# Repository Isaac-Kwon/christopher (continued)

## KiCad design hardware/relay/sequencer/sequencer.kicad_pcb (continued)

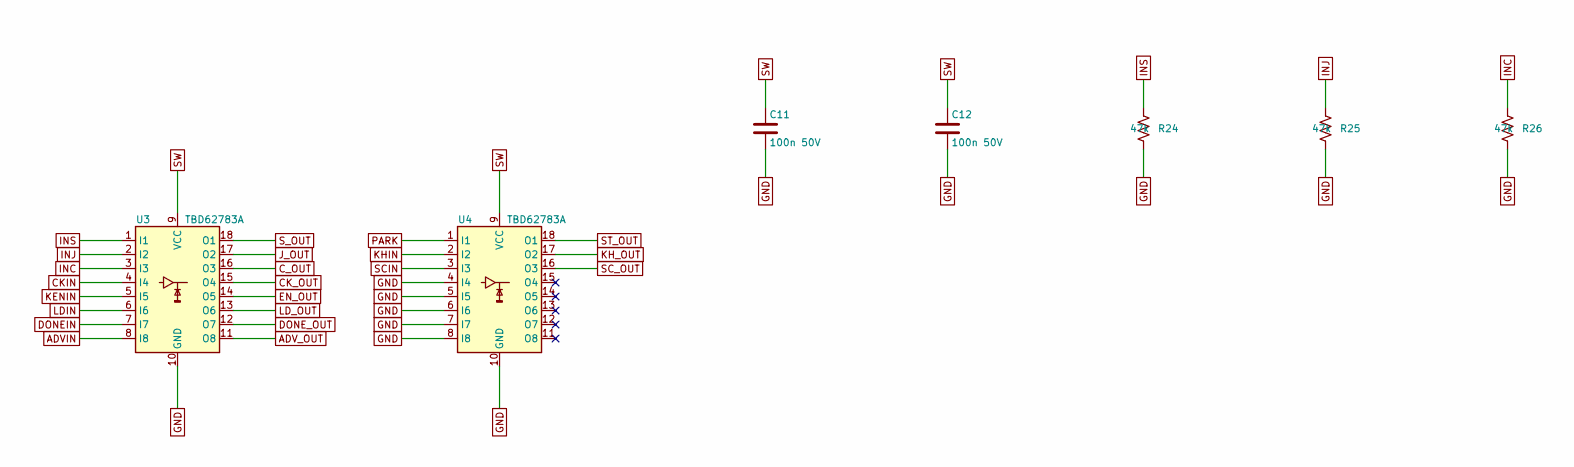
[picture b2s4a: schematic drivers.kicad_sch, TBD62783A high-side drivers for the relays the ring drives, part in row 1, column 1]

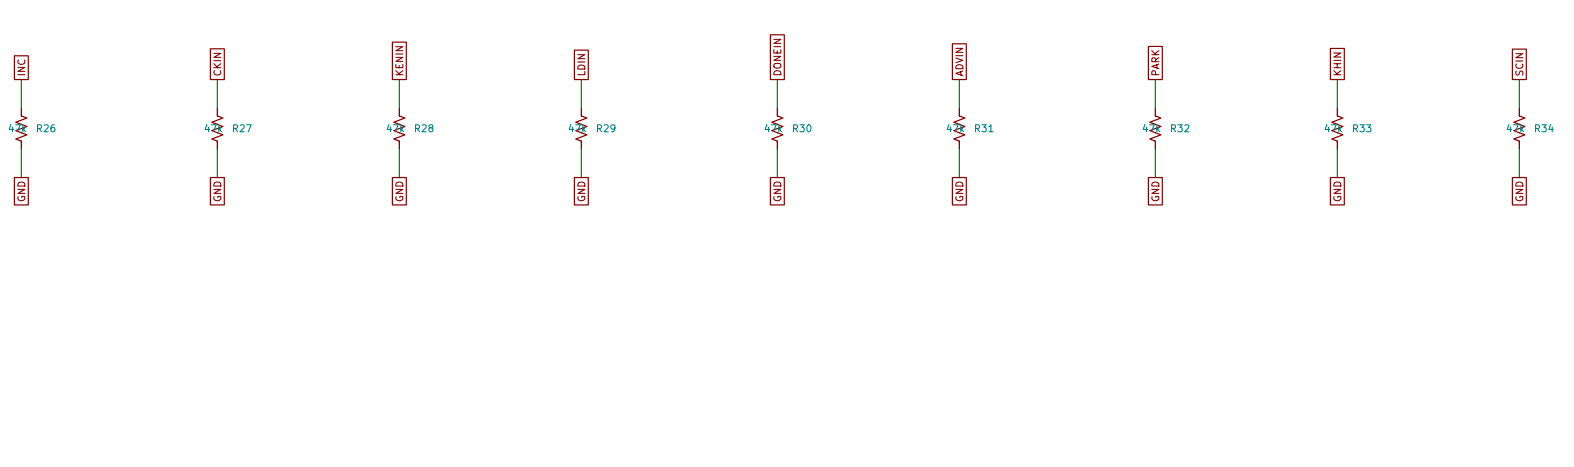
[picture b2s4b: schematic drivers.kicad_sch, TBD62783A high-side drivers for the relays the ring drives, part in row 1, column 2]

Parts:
C11, C12: 100n 50V; C_0805_2012Metric
R24, R25, R26, R27, R28, R29, R30, R31, R32, R33, R34: 47k; R_0603_1608Metric
U3, U4: TBD62783A; SOIC-18W_7.5x11.6mm_P1.27mm

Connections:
ADVIN: R31.1, U3.8 (I8); also elsewhere on the board
ADV_OUT: U3.11 (O8); also elsewhere on the board
CKIN: R27.1, U3.4 (I4); also elsewhere on the board
CK_OUT: U3.15 (O4); also elsewhere on the board
C_OUT: U3.16 (O3); also elsewhere on the board
DONEIN: R30.1, U3.7 (I7); also elsewhere on the board
DONE_OUT: U3.12 (O7); also elsewhere on the board
EN_OUT: U3.14 (O5); also elsewhere on the board
GND: C11.2, C12.2, R24.2, R25.2, R26.2, R27.2, R28.2, R29.2, R30.2, R31.2, R32.2, R33.2, R34.2, U3.10 (GND), U4.4 (I4), U4.5 (I5), U4.6 (I6), U4.7 (I7), U4.8 (I8), U4.10 (GND); also elsewhere on the board
INC: R26.1, U3.3 (I3); also elsewhere on the board
INJ: R25.1, U3.2 (I2); also elsewhere on the board
INS: R24.1, U3.1 (I1); also elsewhere on the board
J_OUT: U3.17 (O2); also elsewhere on the board
KENIN: R28.1, U3.5 (I5); also elsewhere on the board
KHIN: R33.1, U4.2 (I2); also elsewhere on the board
KH_OUT: U4.17 (O2); also elsewhere on the board
LDIN: R29.1, U3.6 (I6); also elsewhere on the board
LD_OUT: U3.13 (O6); also elsewhere on the board
PARK: R32.1, U4.1 (I1); also elsewhere on the board
SCIN: R34.1, U4.3 (I3); also elsewhere on the board
SC_OUT: U4.16 (O3); also elsewhere on the board
ST_OUT: U4.18 (O1); also elsewhere on the board
SW: C11.1, C12.1, U3.9 (VCC), U4.9 (VCC); also elsewhere on the board
S_OUT: U3.18 (O1); also elsewhere on the board

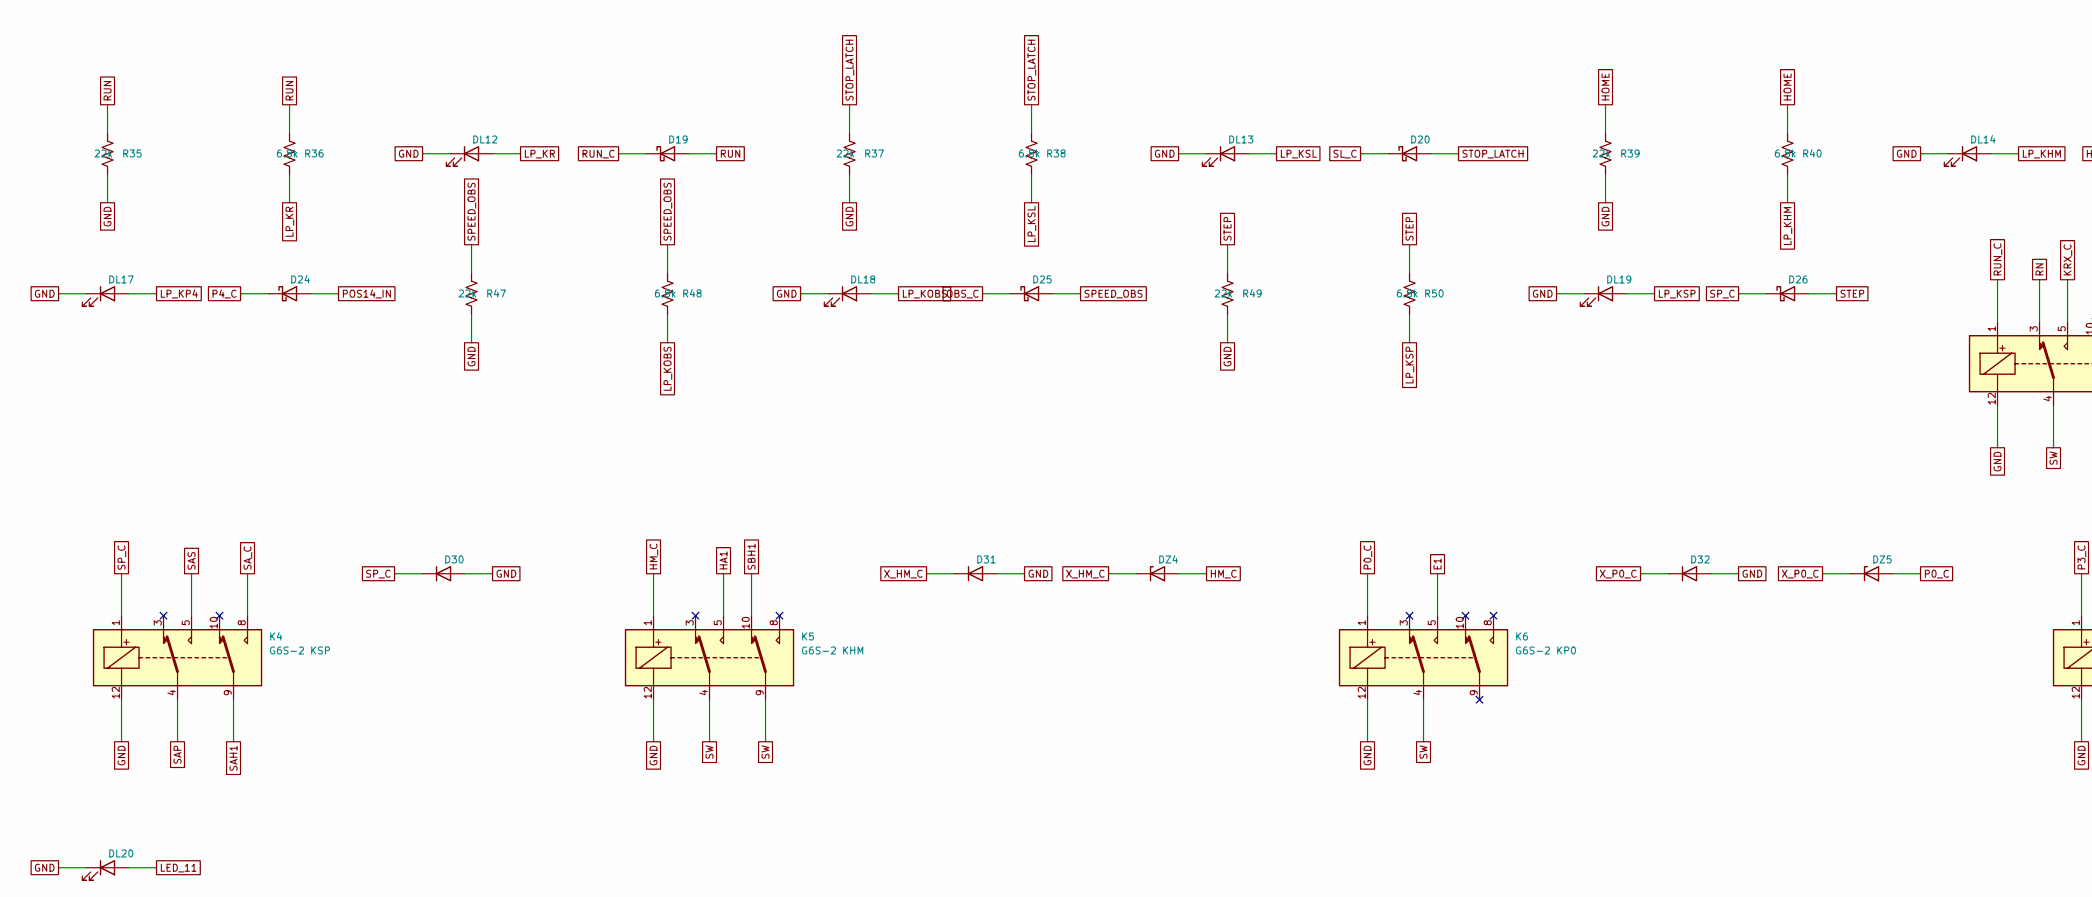
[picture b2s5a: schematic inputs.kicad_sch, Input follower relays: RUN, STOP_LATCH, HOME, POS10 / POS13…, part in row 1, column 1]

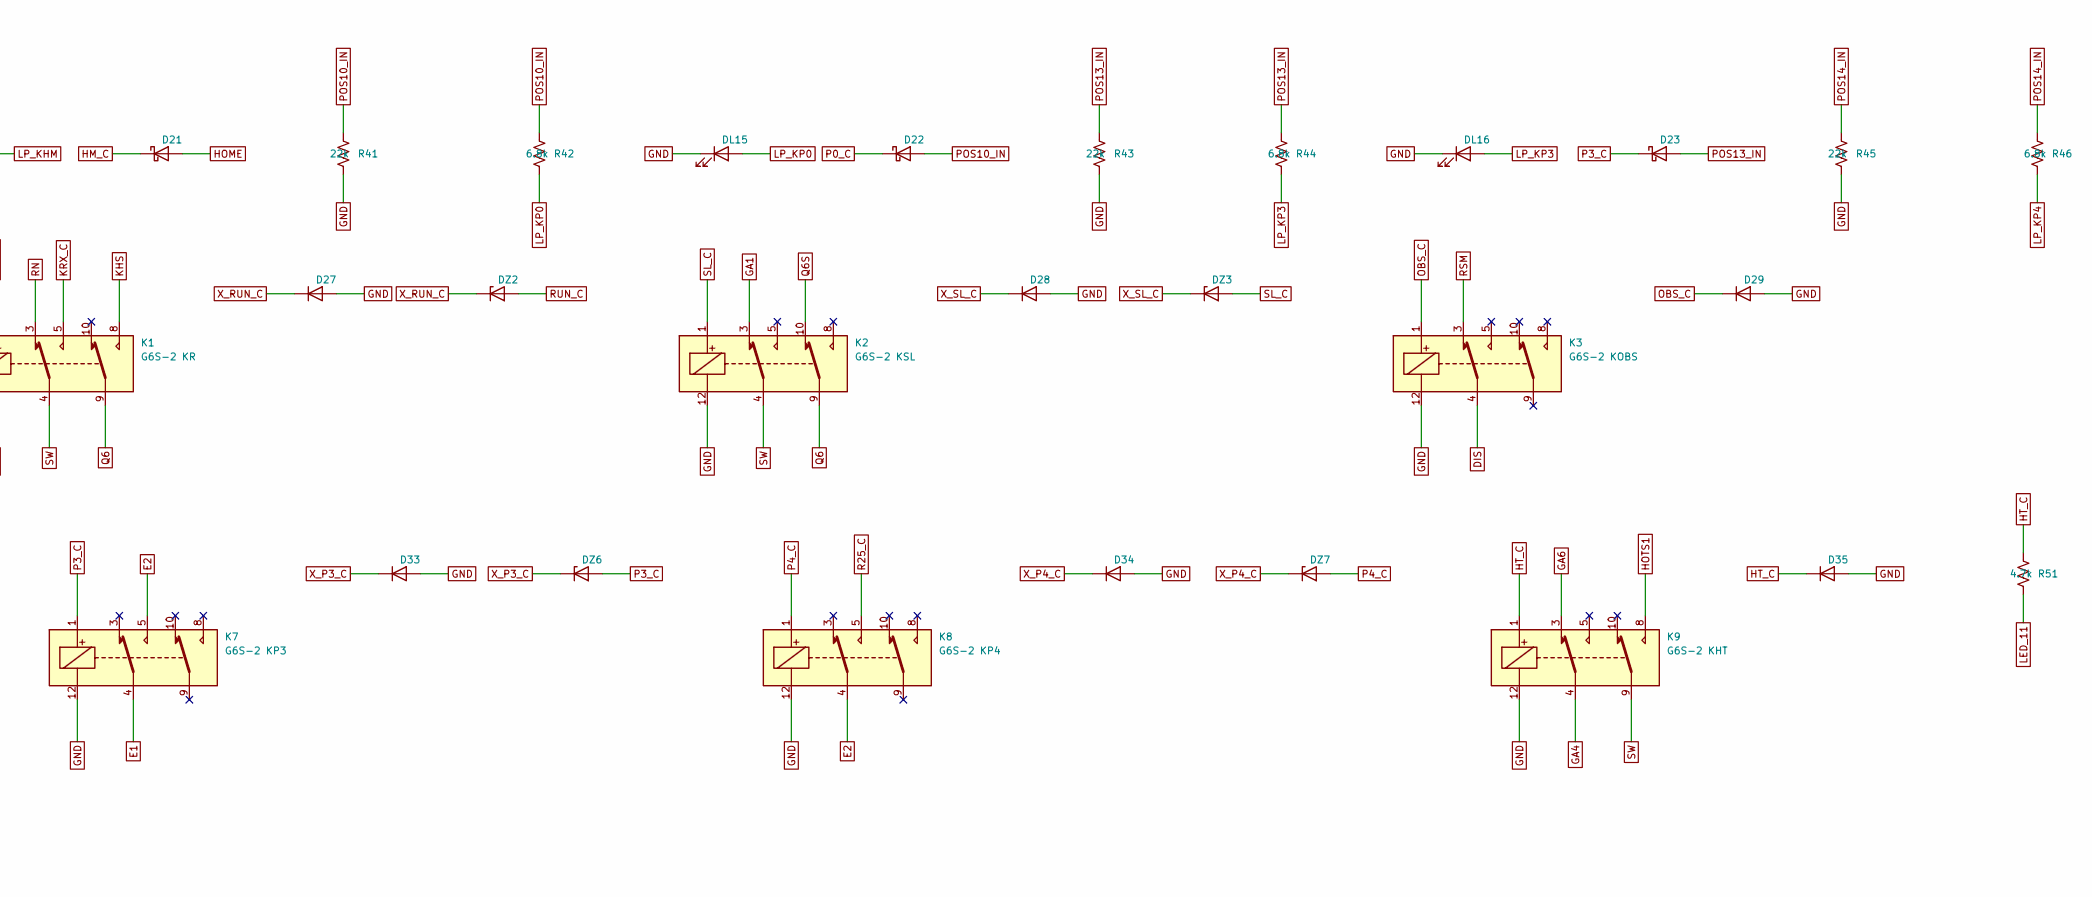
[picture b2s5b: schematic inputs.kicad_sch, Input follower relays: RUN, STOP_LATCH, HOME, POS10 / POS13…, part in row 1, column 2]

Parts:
D19, D20, D21, D22, D23, D24, D25, D26: BAT54 / SS14 Schottky; D_SOD-123
D27, D28, D29, D30, D31, D32, D33, D34, D35: 1N4148W; D_SOD-123
DL12, DL13, DL14, DL15, DL16, DL17, DL18, DL19, DL20: LED; LED_0603_1608Metric
DZ2, DZ3, DZ4, DZ5, DZ6, DZ7: BZT52C30; D_SOD-123
K1: G6S-2 KR; Relay_DPDT_Omron_G6S-2
K2: G6S-2 KSL; Relay_DPDT_Omron_G6S-2
K3: G6S-2 KOBS; Relay_DPDT_Omron_G6S-2
K4: G6S-2 KSP; Relay_DPDT_Omron_G6S-2
K5: G6S-2 KHM; Relay_DPDT_Omron_G6S-2
K6: G6S-2 KP0; Relay_DPDT_Omron_G6S-2
K7: G6S-2 KP3; Relay_DPDT_Omron_G6S-2
K8: G6S-2 KP4; Relay_DPDT_Omron_G6S-2
K9: G6S-2 KHT; Relay_DPDT_Omron_G6S-2
R35, R37, R39, R41, R43, R45, R47, R49: 22k; R_0603_1608Metric
R36, R38, R40, R42, R44, R46, R48, R50: 6.8k; R_0603_1608Metric
R51: 4.7k; R_0603_1608Metric

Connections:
DIS: K3.4; also elsewhere on the board
E1: K6.5, K7.4
E2: K7.5, K8.4
GA1: K2.3; also elsewhere on the board
GA4: K9.4; also elsewhere on the board
GA6: K9.3; also elsewhere on the board
GND: D27.2 (A), D28.2 (A), D29.2 (A), D30.2 (A), D31.2 (A), D32.2 (A), D33.2 (A), D34.2 (A), D35.2 (A), DL12.1 (K), DL13.1 (K), DL14.1 (K), DL15.1 (K), DL16.1 (K), DL17.1 (K), DL18.1 (K), DL19.1 (K), DL20.1 (K), K1.12, K2.12, K3.12, K4.12, K5.12, K6.12, K7.12, K8.12, K9.12, R35.2, R37.2, R39.2, R41.2, R43.2, R45.2, R47.2, R49.2; also elsewhere on the board
HA1: K5.5; also elsewhere on the board
HM_C: D21.1 (K), DZ4.2 (A), K5.1
HOME: D21.2 (A), R39.1, R40.1; also elsewhere on the board
HOTS1: K9.8; also elsewhere on the board
HT_C: D35.1 (K), K9.1, R51.1; also elsewhere on the board
KHS: K1.8; also elsewhere on the board
KRX_C: K1.5; also elsewhere on the board
LED_11: DL20.2 (A), R51.2
LP_KHM: DL14.2 (A), R40.2
LP_KOBS: DL18.2 (A), R48.2
LP_KP0: DL15.2 (A), R42.2
LP_KP3: DL16.2 (A), R44.2
LP_KP4: DL17.2 (A), R46.2
LP_KR: DL12.2 (A), R36.2
LP_KSL: DL13.2 (A), R38.2
LP_KSP: DL19.2 (A), R50.2
OBS_C: D25.1 (K), D29.1 (K), K3.1
P0_C: D22.1 (K), DZ5.2 (A), K6.1
P3_C: D23.1 (K), DZ6.2 (A), K7.1
P4_C: D24.1 (K), DZ7.2 (A), K8.1
POS10_IN: D22.2 (A), R41.1, R42.1; also elsewhere on the board
POS13_IN: D23.2 (A), R43.1, R44.1; also elsewhere on the board
POS14_IN: D24.2 (A), R45.1, R46.1; also elsewhere on the board
Q6: K1.9, K2.9; also elsewhere on the board
Q6S: K2.10; also elsewhere on the board
R25_C: K8.5; also elsewhere on the board
RN: K1.3; also elsewhere on the board
RSM: K3.3; also elsewhere on the board
RUN: D19.2 (A), R35.1, R36.1; also elsewhere on the board
RUN_C: D19.1 (K), DZ2.2 (A), K1.1
SAH1: K4.9; also elsewhere on the board
SAP: K4.4; also elsewhere on the board
SAS: K4.5; also elsewhere on the board
SA_C: K4.8; also elsewhere on the board
SBH1: K5.10; also elsewhere on the board
SL_C: D20.1 (K), DZ3.2 (A), K2.1
SPEED_OBS: D25.2 (A), R47.1, R48.1; also elsewhere on the board
SP_C: D26.1 (K), D30.1 (K), K4.1
STEP: D26.2 (A), R49.1, R50.1; also elsewhere on the board
STOP_LATCH: D20.2 (A), R37.1, R38.1; also elsewhere on the board
SW: K1.4, K2.4, K5.4, K5.9, K6.4, K9.9; also elsewhere on the board
X_HM_C: D31.1 (K), DZ4.1 (K)
X_P0_C: D32.1 (K), DZ5.1 (K)
X_P3_C: D33.1 (K), DZ6.1 (K)
X_P4_C: D34.1 (K), DZ7.1 (K)
X_RUN_C: D27.1 (K), DZ2.1 (K)
X_SL_C: D28.1 (K), DZ3.1 (K)

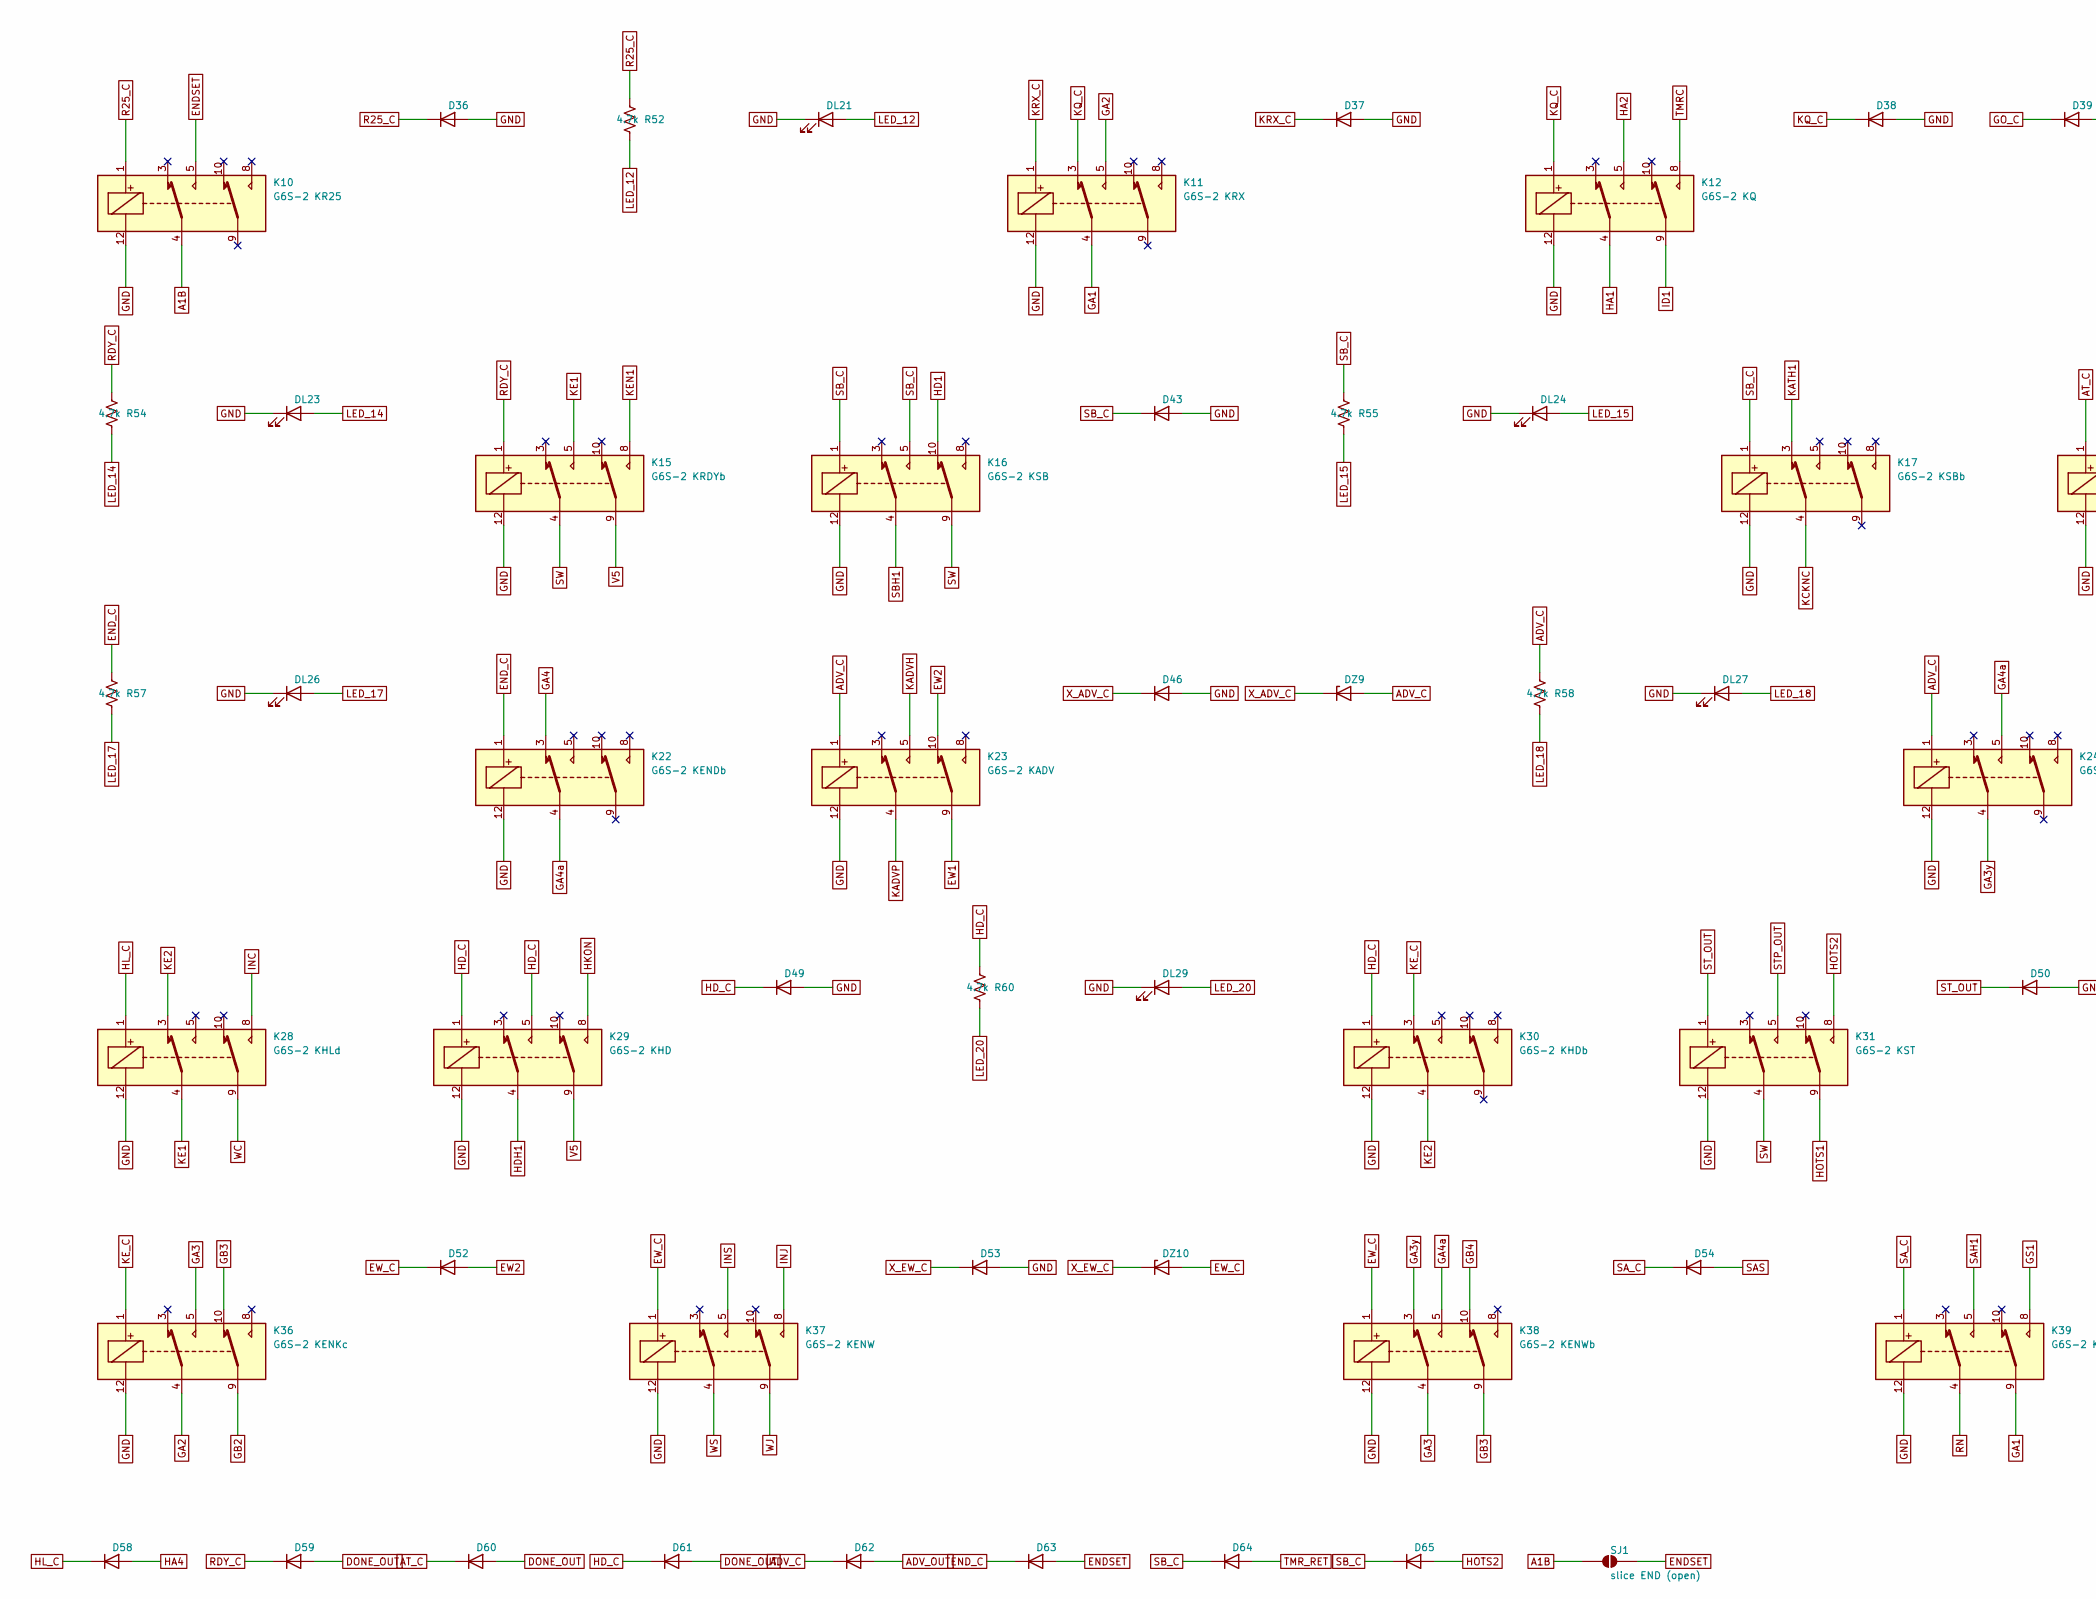
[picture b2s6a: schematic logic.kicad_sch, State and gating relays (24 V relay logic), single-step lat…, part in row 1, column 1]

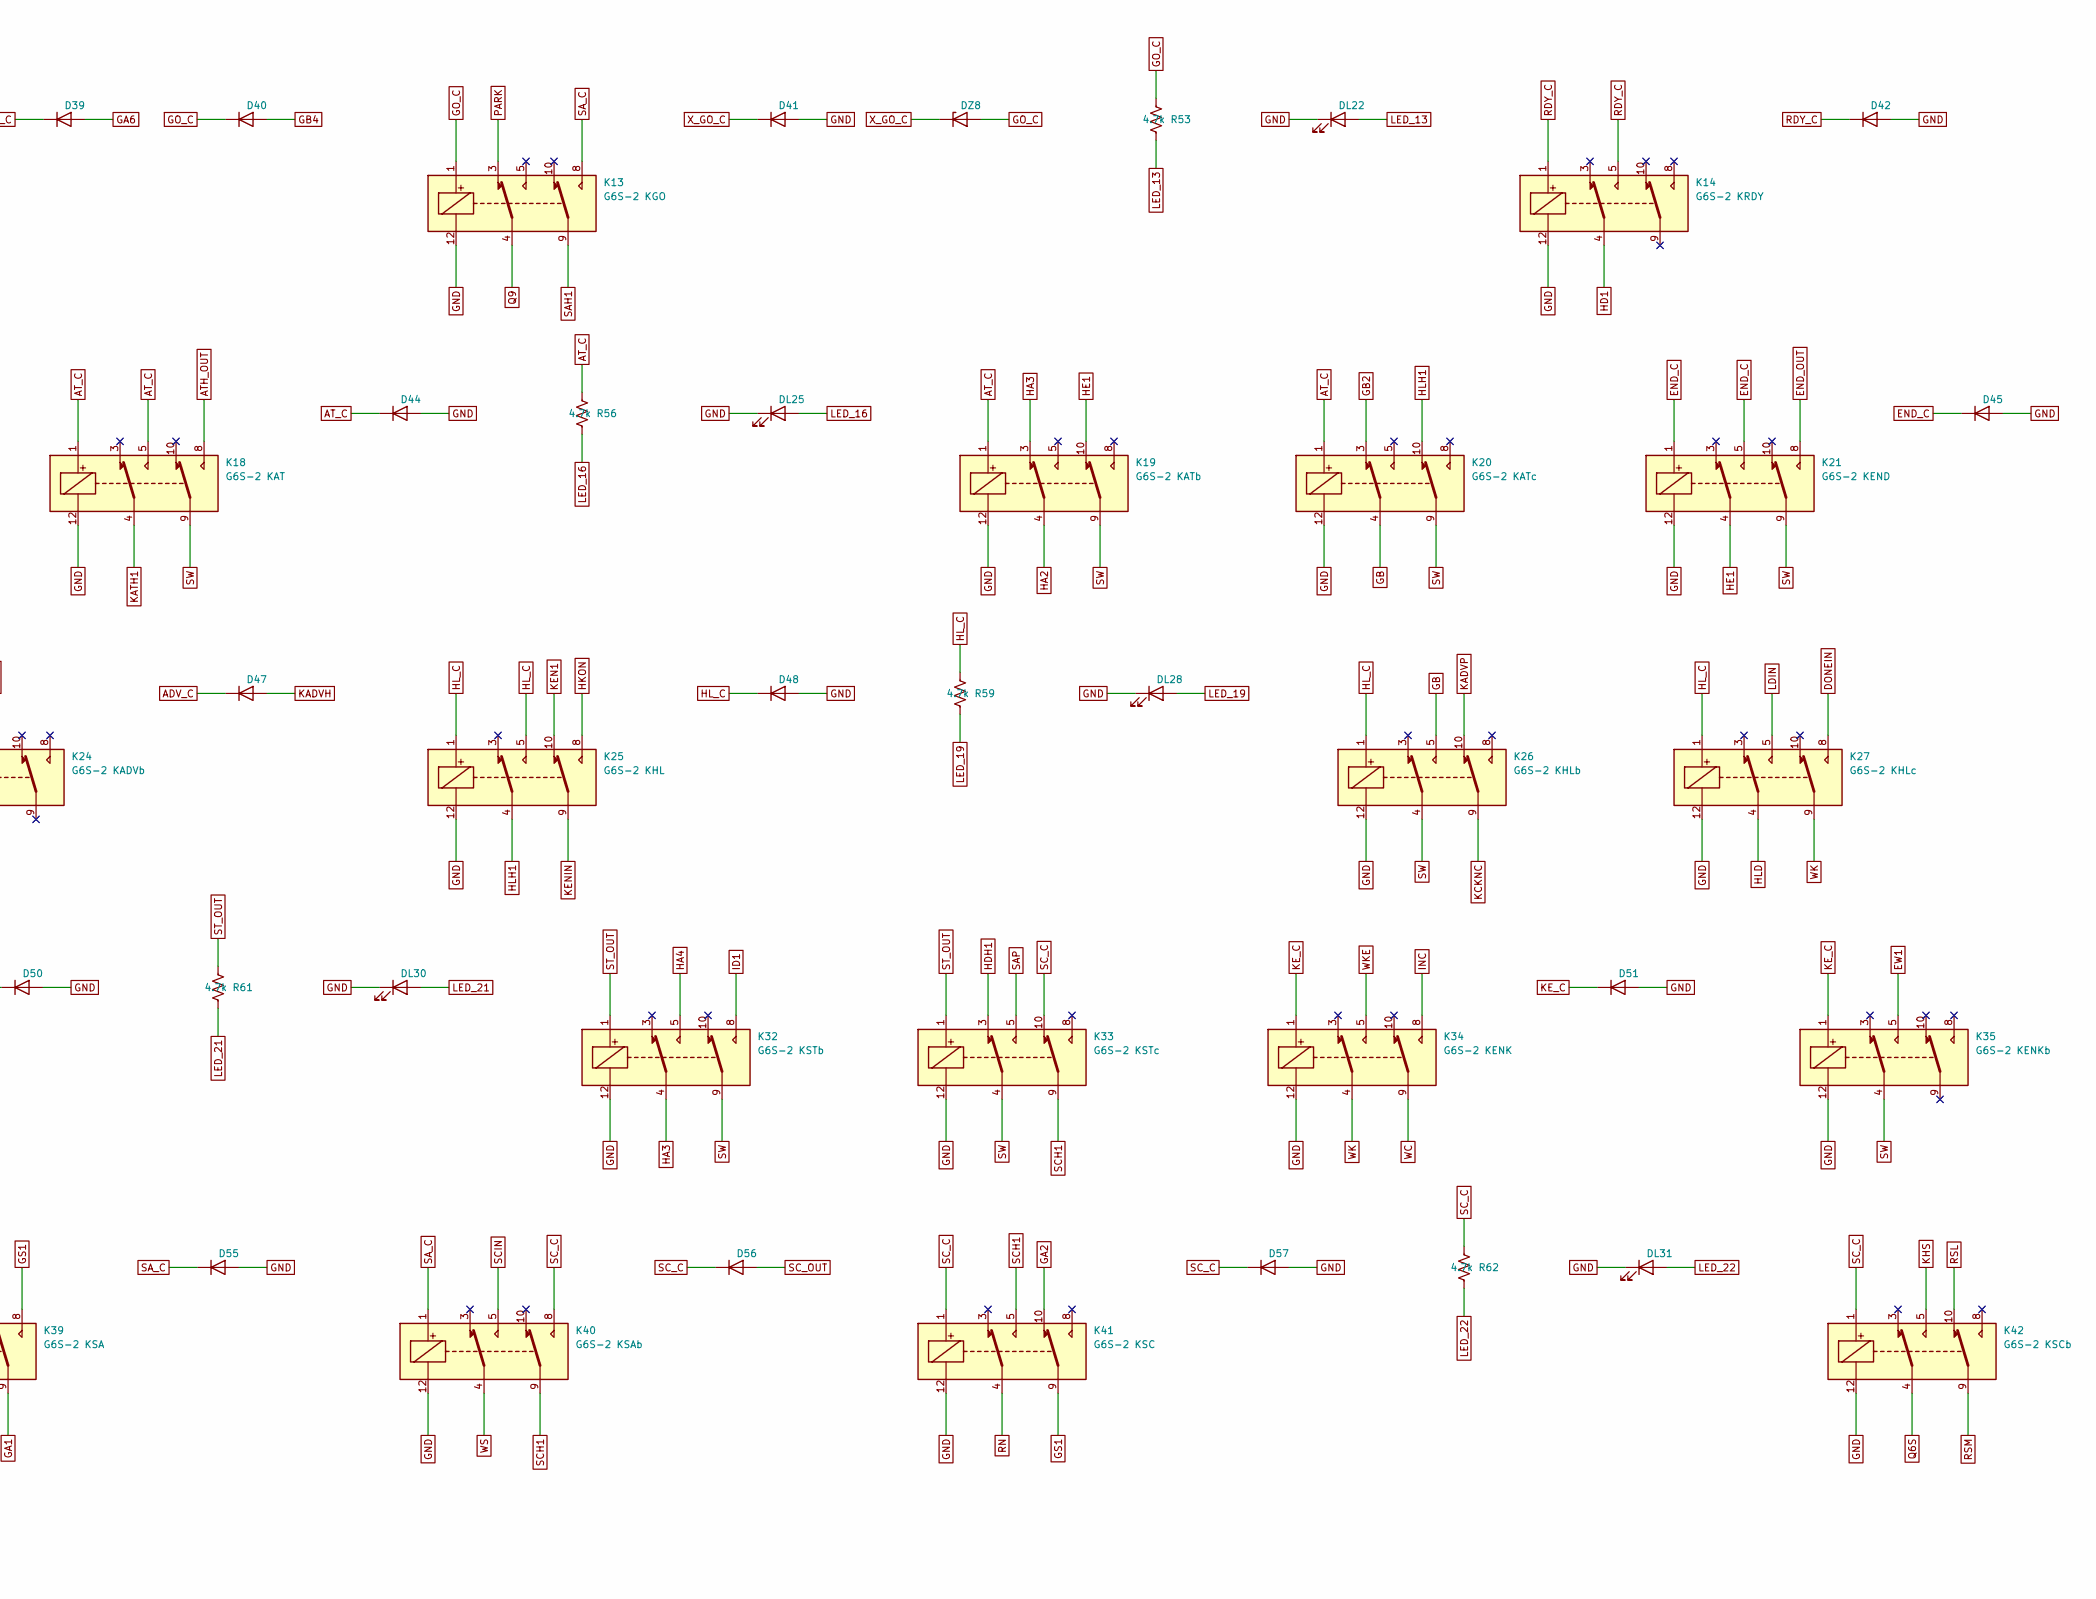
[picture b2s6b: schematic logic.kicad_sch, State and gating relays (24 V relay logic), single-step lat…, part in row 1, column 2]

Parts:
D36, D37, D38, D39, D40, D41, D42, D43, D44, D45, D46, D47, D48, D49, D50, D51, D52, D53, D54, D55, D56, D57, D58, D59, D60, D61, D62, D63, D64, D65: 1N4148W; D_SOD-123
DL21, DL22, DL23, DL24, DL25, DL26, DL27, DL28, DL29, DL30, DL31: LED; LED_0603_1608Metric
DZ8, DZ9, DZ10: BZT52C30; D_SOD-123
K10: G6S-2 KR25; Relay_DPDT_Omron_G6S-2
K11: G6S-2 KRX; Relay_DPDT_Omron_G6S-2
K12: G6S-2 KQ; Relay_DPDT_Omron_G6S-2
K13: G6S-2 KGO; Relay_DPDT_Omron_G6S-2
K14: G6S-2 KRDY; Relay_DPDT_Omron_G6S-2
K15: G6S-2 KRDYb; Relay_DPDT_Omron_G6S-2
K16: G6S-2 KSB; Relay_DPDT_Omron_G6S-2
K17: G6S-2 KSBb; Relay_DPDT_Omron_G6S-2
K18: G6S-2 KAT; Relay_DPDT_Omron_G6S-2
K19: G6S-2 KATb; Relay_DPDT_Omron_G6S-2
K20: G6S-2 KATc; Relay_DPDT_Omron_G6S-2
K21: G6S-2 KEND; Relay_DPDT_Omron_G6S-2
K22: G6S-2 KENDb; Relay_DPDT_Omron_G6S-2
K23: G6S-2 KADV; Relay_DPDT_Omron_G6S-2
K24: G6S-2 KADVb; Relay_DPDT_Omron_G6S-2
K25: G6S-2 KHL; Relay_DPDT_Omron_G6S-2
K26: G6S-2 KHLb; Relay_DPDT_Omron_G6S-2
K27: G6S-2 KHLc; Relay_DPDT_Omron_G6S-2
K28: G6S-2 KHLd; Relay_DPDT_Omron_G6S-2
K29: G6S-2 KHD; Relay_DPDT_Omron_G6S-2
K30: G6S-2 KHDb; Relay_DPDT_Omron_G6S-2
K31: G6S-2 KST; Relay_DPDT_Omron_G6S-2
K32: G6S-2 KSTb; Relay_DPDT_Omron_G6S-2
K33: G6S-2 KSTc; Relay_DPDT_Omron_G6S-2
K34: G6S-2 KENK; Relay_DPDT_Omron_G6S-2
K35: G6S-2 KENKb; Relay_DPDT_Omron_G6S-2
K36: G6S-2 KENKc; Relay_DPDT_Omron_G6S-2
K37: G6S-2 KENW; Relay_DPDT_Omron_G6S-2
K38: G6S-2 KENWb; Relay_DPDT_Omron_G6S-2
K39: G6S-2 KSA; Relay_DPDT_Omron_G6S-2
K40: G6S-2 KSAb; Relay_DPDT_Omron_G6S-2
K41: G6S-2 KSC; Relay_DPDT_Omron_G6S-2
K42: G6S-2 KSCb; Relay_DPDT_Omron_G6S-2
R52, R53, R54, R55, R56, R57, R58, R59, R60, R61, R62: 4.7k; R_0603_1608Metric
SJ1: slice END (open); SolderJumper-2_P1.3mm_Open_RoundedPad1.0x1.5mm

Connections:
A1B: K10.4, SJ1.1 (A); also elsewhere on the board
ADV_C: D47.1 (K), D62.1 (K), DZ9.2 (A), K23.1, K24.1, R58.1
ADV_OUT: D62.2 (A); also elsewhere on the board
ATH_OUT: K18.8; also elsewhere on the board
AT_C: D44.1 (K), D60.1 (K), K18.1, K18.5, K19.1, K20.1, R56.1
DONEIN: K27.8; also elsewhere on the board
DONE_OUT: D59.2 (A), D60.2 (A), D61.2 (A); also elsewhere on the board
ENDSET: D63.2 (A), K10.5, SJ1.2 (B)
END_C: D45.1 (K), D63.1 (K), K21.1, K21.5, K22.1, R57.1
END_OUT: K21.8; also elsewhere on the board
EW1: K23.9, K35.5
EW2: D52.2 (A), K23.10
EW_C: D52.1 (K), DZ10.2 (A), K37.1, K38.1
GA1: K11.4, K39.9; also elsewhere on the board
GA2: K11.5, K36.4, K41.10
GA3: K36.5, K38.4
GA3y: K24.4, K38.3
GA4: K22.3; also elsewhere on the board
GA4a: K22.4, K24.5, K38.5
GA6: D39.2 (A); also elsewhere on the board
GB: K20.4, K26.5
GB2: K20.3, K36.9
GB3: K36.10, K38.9
GB4: D40.2 (A), K38.10
GND: D36.2 (A), D37.2 (A), D38.2 (A), D41.2 (A), D42.2 (A), D43.2 (A), D44.2 (A), D45.2 (A), D46.2 (A), D48.2 (A), D49.2 (A), D50.2 (A), D51.2 (A), D53.2 (A), D55.2 (A), D57.2 (A), DL21.1 (K), DL22.1 (K), DL23.1 (K), DL24.1 (K), DL25.1 (K), DL26.1 (K), DL27.1 (K), DL28.1 (K), DL29.1 (K), DL30.1 (K), DL31.1 (K), K10.12, K11.12, K12.12, K13.12, K14.12, K15.12, K16.12, K17.12, K18.12, K19.12, K20.12, K21.12, K22.12, K23.12, K24.12, K25.12, K26.12, K27.12, K28.12, K29.12, K30.12, K31.12, K32.12, K33.12, K34.12, K35.12, K36.12, K37.12, K38.12, K39.12, K40.12, K41.12, K42.12; also elsewhere on the board
GO_C: D39.1 (K), D40.1 (K), DZ8.2 (A), K13.1, R53.1
GS1: K39.8, K41.9
HA1: K12.4; also elsewhere on the board
HA2: K12.5, K19.4
HA3: K19.3, K32.4
HA4: D58.2 (A), K32.5
HD1: K14.4, K16.10
HDH1: K29.4, K33.3
HD_C: D49.1 (K), D61.1 (K), K29.1, K29.5, K30.1, R60.1
HE1: K19.10, K21.4
HKON: K25.8, K29.8; also elsewhere on the board
HLD: K27.4; also elsewhere on the board
HLH1: K20.10, K25.4
HL_C: D48.1 (K), D58.1 (K), K25.1, K25.5, K26.1, K27.1, K28.1, R59.1
HOTS1: K31.9; also elsewhere on the board
HOTS2: D65.2 (A), K31.8
ID1: K12.9, K32.8
INC: K28.8, K34.8; also elsewhere on the board
INJ: K37.8; also elsewhere on the board
INS: K37.5; also elsewhere on the board
KADVH: D47.2 (A), K23.5
KADVP: K23.4, K26.10
KATH1: K17.3, K18.4
KCKNC: K17.4, K26.9; also elsewhere on the board
KE1: K15.5, K28.4
KE2: K28.3, K30.4
KEN1: K15.8, K25.10
KENIN: K25.9; also elsewhere on the board
KE_C: D51.1 (K), K30.3, K34.1, K35.1, K36.1
KHS: K42.5; also elsewhere on the board
KQ_C: D38.1 (K), K11.3, K12.1
KRX_C: D37.1 (K), K11.1; also elsewhere on the board
LDIN: K27.5; also elsewhere on the board
LED_12: DL21.2 (A), R52.2
LED_13: DL22.2 (A), R53.2
LED_14: DL23.2 (A), R54.2
LED_15: DL24.2 (A), R55.2
LED_16: DL25.2 (A), R56.2
LED_17: DL26.2 (A), R57.2
LED_18: DL27.2 (A), R58.2
LED_19: DL28.2 (A), R59.2
LED_20: DL29.2 (A), R60.2
LED_21: DL30.2 (A), R61.2
LED_22: DL31.2 (A), R62.2
PARK: K13.3; also elsewhere on the board
Q6S: K42.4; also elsewhere on the board
Q9: K13.4; also elsewhere on the board
R25_C: D36.1 (K), K10.1, R52.1; also elsewhere on the board
RDY_C: D42.1 (K), D59.1 (K), K14.1, K14.5, K15.1, R54.1
RN: K39.4, K41.4; also elsewhere on the board
RSL: K42.10; also elsewhere on the board
RSM: K42.9; also elsewhere on the board
SAH1: K13.9, K39.5; also elsewhere on the board
SAP: K33.5; also elsewhere on the board
SAS: D54.2 (A); also elsewhere on the board
SA_C: D54.1 (K), D55.1 (K), K13.8, K39.1, K40.1; also elsewhere on the board
SBH1: K16.4; also elsewhere on the board
SB_C: D43.1 (K), D64.1 (K), D65.1 (K), K16.1, K16.5, K17.1, R55.1
SCH1: K33.9, K40.9, K41.5
SCIN: K40.5; also elsewhere on the board
SC_C: D56.1 (K), D57.1 (K), K33.10, K40.8, K41.1, K42.1, R62.1
SC_OUT: D56.2 (A); also elsewhere on the board
STP_OUT: K31.5; also elsewhere on the board
ST_OUT: D50.1 (K), K31.1, K32.1, K33.1, R61.1; also elsewhere on the board
SW: K15.4, K16.9, K18.9, K19.9, K20.9, K21.9, K26.4, K31.4, K32.9, K33.4, K35.4; also elsewhere on the board
TMRC: K12.8; also elsewhere on the board
TMR_RET: D64.2 (A); also elsewhere on the board
V5: K15.9, K29.9; also elsewhere on the board
WC: K28.9, K34.9; also elsewhere on the board
WJ: K37.9; also elsewhere on the board
WK: K27.9, K34.4; also elsewhere on the board
WKE: K34.5; also elsewhere on the board
WS: K37.4, K40.4; also elsewhere on the board
X_ADV_C: D46.1 (K), DZ9.1 (K)
X_EW_C: D53.1 (K), DZ10.1 (K)
X_GO_C: D41.1 (K), DZ8.1 (K)
